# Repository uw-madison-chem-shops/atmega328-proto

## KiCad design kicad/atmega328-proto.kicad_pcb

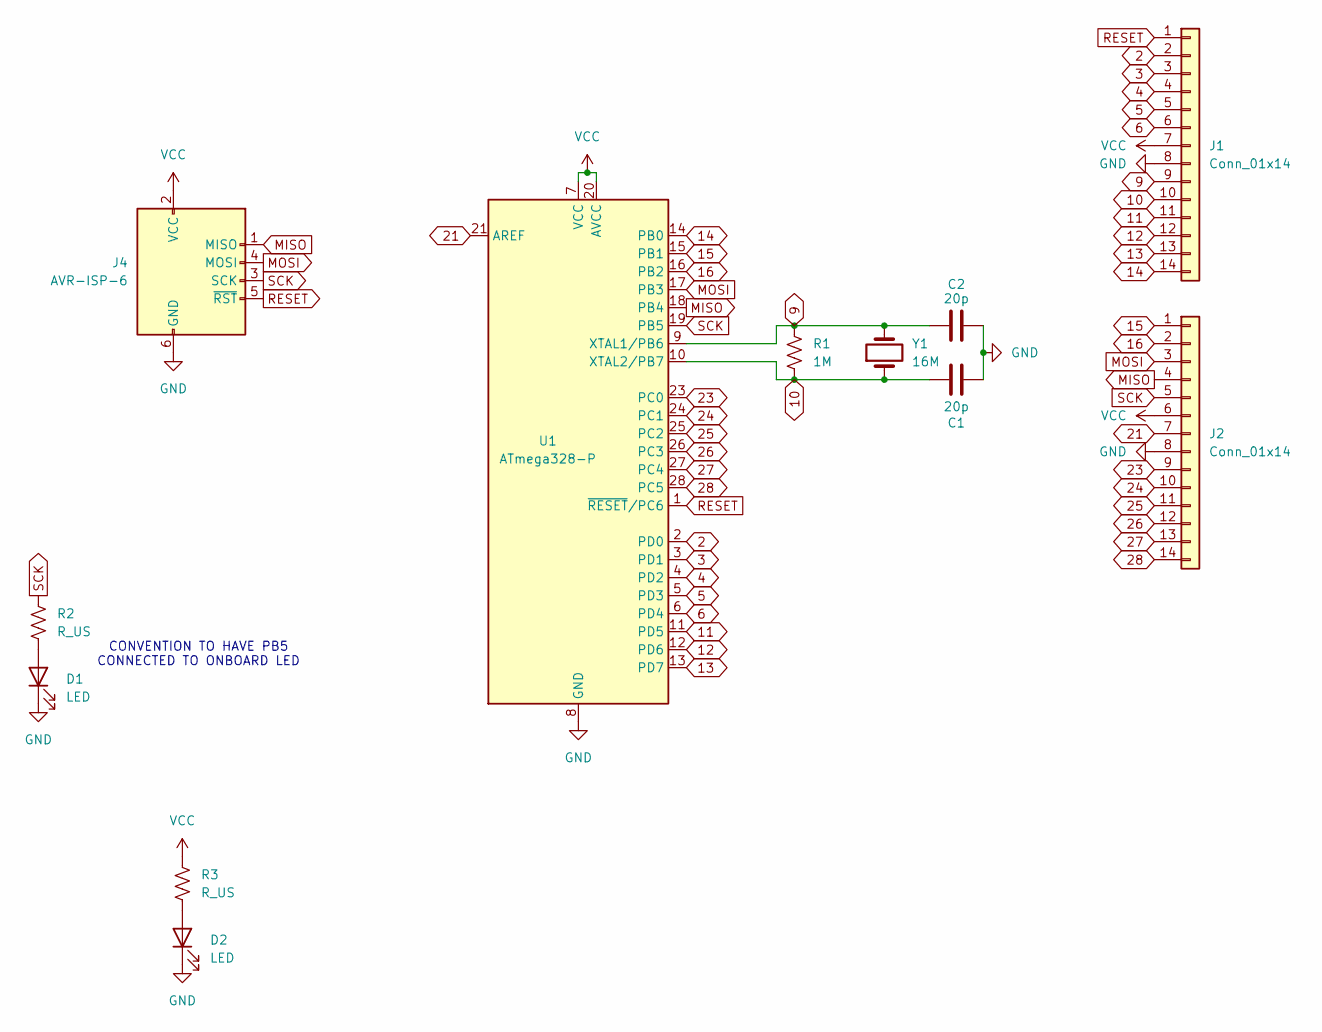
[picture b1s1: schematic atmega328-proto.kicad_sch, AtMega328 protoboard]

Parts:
C1, C2: 20p; C_1206_3216Metric_Pad1.33x1.80mm_HandSolder
D1, D2: LED; LED_1206_3216Metric_Pad1.42x1.75mm_HandSolder
J1, J2: Conn_01x14; PinHeader_1x14_P2.54mm_Vertical
J4: AVR-ISP-6; PinHeader_2x03_P2.54mm_Vertical
R1: 1M; R_1206_3216Metric
R2, R3: R_US; R_1206_3216Metric_Pad1.30x1.75mm_HandSolder
U1: ATmega328-P; DIP-28_W7.62mm
Y1: 16M; Crystal_HC49-U_Vertical

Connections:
2: J1.2, U1.2 (PD0)
3: J1.3, U1.3 (PD1)
4: J1.4, U1.4 (PD2)
5: J1.5, U1.5 (PD3)
6: J1.6, U1.6 (PD4)
9: C2.1, J1.9, R1.1, U1.9 (XTAL1/PB6), Y1.2
10: C1.2, J1.10, R1.2, U1.10 (XTAL2/PB7), Y1.1
11: J1.11, U1.11 (PD5)
12: J1.12, U1.12 (PD6)
13: J1.13, U1.13 (PD7)
14: J1.14, U1.14 (PB0)
15: J2.1, U1.15 (PB1)
16: J2.2, U1.16 (PB2)
21: J2.7, U1.21 (AREF)
23: J2.9, U1.23 (PC0)
24: J2.10, U1.24 (PC1)
25: J2.11, U1.25 (PC2)
26: J2.12, U1.26 (PC3)
27: J2.13, U1.27 (PC4)
28: J2.14, U1.28 (PC5)
GND: C1.1, C2.2, D1.1 (K), D2.1 (K), J1.8, J2.8, J4.6 (GND), U1.8 (GND), U1.22 (GND)
MISO: J2.4, J4.1 (MISO), U1.18 (PB4)
MOSI: J2.3, J4.4 (MOSI), U1.17 (PB3)
unnamed: D1.2 (A), R2.2
unnamed: D2.2 (A), R3.2
RESET: J1.1, J4.5 (~RST), U1.1 (~RESET/PC6)
SCK: J2.5, J4.3 (SCK), R2.1, U1.19 (PB5)
VCC: J1.7, J2.6, J4.2 (VCC), R3.1, U1.7 (VCC), U1.20 (AVCC)

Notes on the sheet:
CONVENTION TO HAVE PB5 CONNECTED TO ONBOARD LED

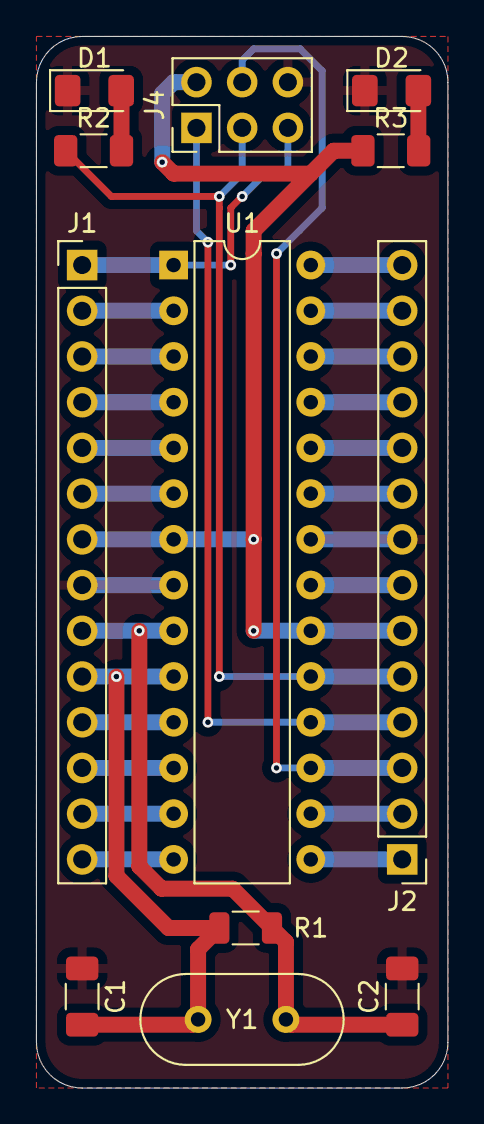
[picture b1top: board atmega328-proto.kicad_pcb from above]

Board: 2 copper layers, 22.9 x 58.4 mm, 12 parts (0 on the bottom side), 28 nets.

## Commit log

2024-05-10 revA
